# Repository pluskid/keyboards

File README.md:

# KID's Keyboard Related Code

- [flanck](flanck/): contains the PCB, plates and firmware of my first self-designed keyboard.
- [ortho-keymap](ortho-keymap/): a script that I use to manage and convert my ([Colemak-DHm](https://colemakmods.github.io/mod-dh/keyboards.html) based) keymap across multiple different ortholinear flavored keyboards (Flanck, Planck, Corne and Reviung41).
- [crkbd-kid](crkbd-kid/): my custom firmware for the [Corne](https://github.com/foostan/crkbd) split keyboard, mostly containing the code for custom OLED display.

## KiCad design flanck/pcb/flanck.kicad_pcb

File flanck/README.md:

# Flanck

Flanck is the "Fat Planck". It is a low profile 4x12 grid style keypoard using Kailh Choc Switch. The outer most columns are modified to be 1.5U wide to make it easier to hit without stretching the wrist too much. The two sides are also made 1U apart to make it more ergonomic. It also makes room for the Elite-C on the top side of the PCB, which allows us to reduce the height of the board.

## Flanck v1.1

The first built of Flanck (on Oct. 27, 2020). If you are interested in building this keyboard yourself, you will need the followings:

- The garber files of the PCB, the top plate and bottom plate can be found in the [Flanck v1.1 Release page](https://github.com/pluskid/keyboards/releases/tag/flanck-v1.1). You can order PCBs using those files from manufactures like [JLCPCB](https://jlcpcb.com/).
- The firmware is based on [QMK](https://docs.qmk.fm/), and can be found under [qmk/v1](qmk/v1/).
- The following table list the remaining components that are needed. The links are only provided for conveinence. You can collect your parts from any sources.

| Item        | Qty| Links | Remarks |
|-------------|---:|-------|---------|
| Elite-C     |  1 | [BoardSource](https://boardsource.xyz/store/5ef67ea66786dc1e65a80708), [Keeb.io](https://keeb.io/products/elite-c-low-profile-version-usb-c-pro-micro-replacement-atmega32u4) | Can also use Pro Micro and compatible clones -- then don't forget to update `BOOTLOADER` in [qmk/v1/rules.mk](qmk/v1/rules.mk) of the firmware accordinly. |
| Diode (1N4148 SMD) | 48 | [BoardSource](https://boardsource.xyz/store/5ec9fc5d64caf04f83aa646c) | |
| Choc Hotswap Socket| 48 | [BoardSource](https://boardsource.xyz/store/5eca381464caf04f83aa6482) | |
| Kailh Choc Switch  | 48 | [BoardSource](https://boardsource.xyz/store/5ef6eff1de8f0374b7347742), [AliExperss](https://www.aliexpress.com/item/4000907409650.html) | Both V1 and V2 should work, though I only tested Choc V1 |
| Choc Keycap 1U | 40 | [BoardSource MBK keycaps](https://boardsource.xyz/store/5f6ef2d68e3bf05ab838f918)| Get 2x home-scooped 1U keycaps as well |
| Choc Keycap 1.5U | 8 | [BoardSource MBK keycaps](https://boardsource.xyz/store/5f6ef2d68e3bf05ab838f918)| |
| Tact Switch |  1 | [Amazon](https://www.amazon.com/gp/product/B0819VWGX8/ref=ppx_yo_dt_b_asin_title_o09_s00?ie=UTF8&psc=1), [AliExperss](https://www.aliexpress.com/item/32914876022.html) | For the reset button |
| Rubber Feet |  6 | [Amazon](https://www.amazon.com/gp/product/B07LGK6RWN/ref=ppx_yo_dt_b_asin_title_o00_s00?ie=UTF8&psc=1), [AliExperss](https://www.aliexpress.com/item/32289191938.html) | |
| M2 4mm spacer | 7 | [Amazon](https://www.amazon.com/gp/product/B07H3VN9Y9/ref=ppx_yo_dt_b_asin_title_o02_s00?ie=UTF8&psc=1) | Longer spacers also work, though board will be higher |
| M2 screws     | 14 | [BoardSource](https://boardsource.xyz/store/5ecad681e7e0515b382b553e) | 4mm screws work for 4mm spacers. You can get some M2 washers (1mm thick) to fine tune if your spacers do not have enough room for the screws to go all the way in. |
| USB-C cable |  1 | [Amazon](https://www.amazon.com/gp/product/B07X8FNQ6K/ref=ppx_yo_dt_b_asin_title_o02_s01?ie=UTF8&psc=1) | USB-2 is enougn |
| Washers or O rings | | | Optional. See below. |

## Washers / O rings between PCB and Bottom Plate

When using Choc switches, there is ~2mm space between the PCB and the bottom plate. The PCB is held together with the top plate by the switches. If you frequently change the switches or want extra support for the PCB, you can put washers or O rings around each M2 spacer between the PCB and the bottom plate. See the illustration below:

## Wireless Flanck with nice!nano

You can use any Pro Micro compatible MCU board in place of Elite-C. In particular, I built a [nice!nano](https://docs.nicekeyboards.com/#/nice!nano/) based Flanck keyboard that support bluetooth. I use [this 3.7V 100mAh Lithium Ion Polymer Battery](https://www.amazon.com/gp/product/B0137KTPP0/ref=ppx_yo_dt_b_search_asin_title?ie=UTF8&psc=1), which is small enough to sit below the nice!nano. The [ZMK](https://zmkfirmware.dev/) based firmware can be found [here](https://github.com/pluskid/flanck-zmk-config).

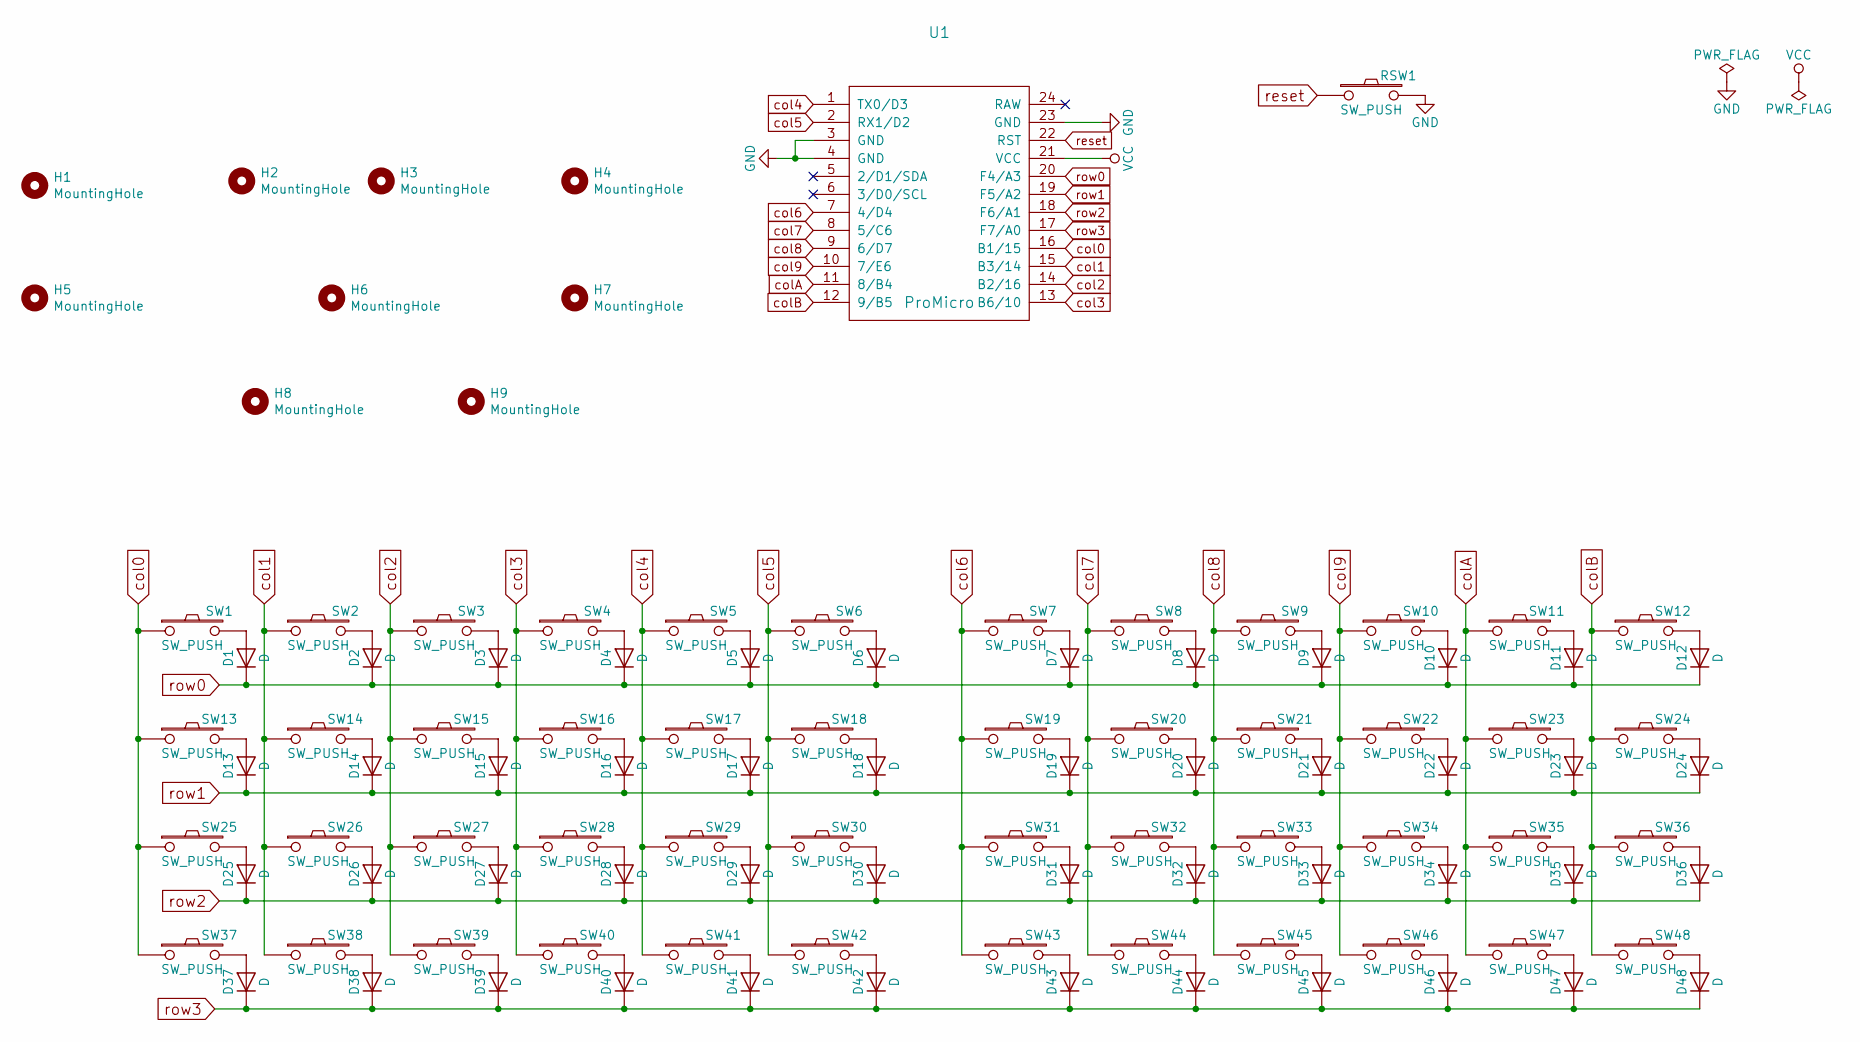
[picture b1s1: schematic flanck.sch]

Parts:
D1, D2, D3, D4, D5, D6, D7, D8, D9, D10, D11, D12, D13, D14, D15, D16, D17, D18, D19, D20, D21, D22, D23, D24, D25, D26, D27, D28, D29, D30, D31, D32, D33, D34, D35, D36, D37, D38, D39, D40, D41, D42, D43, D44, D45, D46, D47, D48: D; D3_SMD_v2
H1, H2, H3, H4, H5, H6, H7, H8, H9: MountingHole; M2_Threads_v2
RSW1: SW_PUSH; ResetSW_1side
SW1, SW12, SW13, SW24, SW25, SW36, SW42, SW43: SW_PUSH; ChocV1_V2_Hotswap_1.5u
SW2, SW3, SW4, SW5, SW6, SW7, SW8, SW9, SW10, SW11, SW14, SW15, SW16, SW17, SW18, SW19, SW20, SW21, SW22, SW23, SW26, SW27, SW28, SW29, SW30, SW31, SW32, SW33, SW34, SW35, SW37, SW38, SW39, SW40, SW41, SW44, SW45, SW46, SW47, SW48: SW_PUSH; ChocV1_V2_Hotswap
U1: ProMicro; ProMicro_v3

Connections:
GND: RSW1.2, U1.3 (GND), U1.4 (GND), U1.23 (GND)
unnamed: D1.2 (A), SW1.2
unnamed: D2.2 (A), SW2.2
unnamed: D3.2 (A), SW3.2
unnamed: D4.2 (A), SW4.2
unnamed: D5.2 (A), SW5.2
unnamed: D6.2 (A), SW6.2
unnamed: D7.2 (A), SW7.2
unnamed: D8.2 (A), SW8.2
unnamed: D9.2 (A), SW9.2
unnamed: D10.2 (A), SW10.2
unnamed: D11.2 (A), SW11.2
unnamed: D12.2 (A), SW12.2
unnamed: D13.2 (A), SW13.2
unnamed: D14.2 (A), SW14.2
unnamed: D15.2 (A), SW15.2
unnamed: D16.2 (A), SW16.2
unnamed: D17.2 (A), SW17.2
unnamed: D18.2 (A), SW18.2
unnamed: D19.2 (A), SW19.2
unnamed: D20.2 (A), SW20.2
unnamed: D21.2 (A), SW21.2
unnamed: D22.2 (A), SW22.2
unnamed: D23.2 (A), SW23.2
unnamed: D24.2 (A), SW24.2
unnamed: D25.2 (A), SW25.2
unnamed: D26.2 (A), SW26.2
unnamed: D27.2 (A), SW27.2
unnamed: D28.2 (A), SW28.2
unnamed: D29.2 (A), SW29.2
unnamed: D30.2 (A), SW30.2
unnamed: D31.2 (A), SW31.2
unnamed: D32.2 (A), SW32.2
unnamed: D33.2 (A), SW33.2
unnamed: D34.2 (A), SW34.2
unnamed: D35.2 (A), SW35.2
unnamed: D36.2 (A), SW36.2
unnamed: D37.2 (A), SW37.2
unnamed: D38.2 (A), SW38.2
unnamed: D39.2 (A), SW39.2
unnamed: D40.2 (A), SW40.2
unnamed: D41.2 (A), SW41.2
unnamed: D42.2 (A), SW42.2
unnamed: D43.2 (A), SW43.2
unnamed: D44.2 (A), SW44.2
unnamed: D45.2 (A), SW45.2
unnamed: D46.2 (A), SW46.2
unnamed: D47.2 (A), SW47.2
unnamed: D48.2 (A), SW48.2
VCC: U1.21 (VCC)
col0: SW1.1, SW13.1, SW25.1, SW37.1, U1.16 (B1/15)
col1: SW2.1, SW14.1, SW26.1, SW38.1, U1.15 (B3/14)
col2: SW3.1, SW15.1, SW27.1, SW39.1, U1.14 (B2/16)
col3: SW4.1, SW16.1, SW28.1, SW40.1, U1.13 (B6/10)
col4: SW5.1, SW17.1, SW29.1, SW41.1, U1.1 (TX0/D3)
col5: SW6.1, SW18.1, SW30.1, SW42.1, U1.2 (RX1/D2)
col6: SW7.1, SW19.1, SW31.1, SW43.1, U1.7 (4/D4)
col7: SW8.1, SW20.1, SW32.1, SW44.1, U1.8 (5/C6)
col8: SW9.1, SW21.1, SW33.1, SW45.1, U1.9 (6/D7)
col9: SW10.1, SW22.1, SW34.1, SW46.1, U1.10 (7/E6)
colA: SW11.1, SW23.1, SW35.1, SW47.1, U1.11 (8/B4)
colB: SW12.1, SW24.1, SW36.1, SW48.1, U1.12 (9/B5)
reset: RSW1.1, U1.22 (RST)
row0: D1.1 (K), D2.1 (K), D3.1 (K), D4.1 (K), D5.1 (K), D6.1 (K), D7.1 (K), D8.1 (K), D9.1 (K), D10.1 (K), D11.1 (K), D12.1 (K), U1.20 (F4/A3)
row1: D13.1 (K), D14.1 (K), D15.1 (K), D16.1 (K), D17.1 (K), D18.1 (K), D19.1 (K), D20.1 (K), D21.1 (K), D22.1 (K), D23.1 (K), D24.1 (K), U1.19 (F5/A2)
row2: D25.1 (K), D26.1 (K), D27.1 (K), D28.1 (K), D29.1 (K), D30.1 (K), D31.1 (K), D32.1 (K), D33.1 (K), D34.1 (K), D35.1 (K), D36.1 (K), U1.18 (F6/A1)
row3: D37.1 (K), D38.1 (K), D39.1 (K), D40.1 (K), D41.1 (K), D42.1 (K), D43.1 (K), D44.1 (K), D45.1 (K), D46.1 (K), D47.1 (K), D48.1 (K), U1.17 (F7/A0)

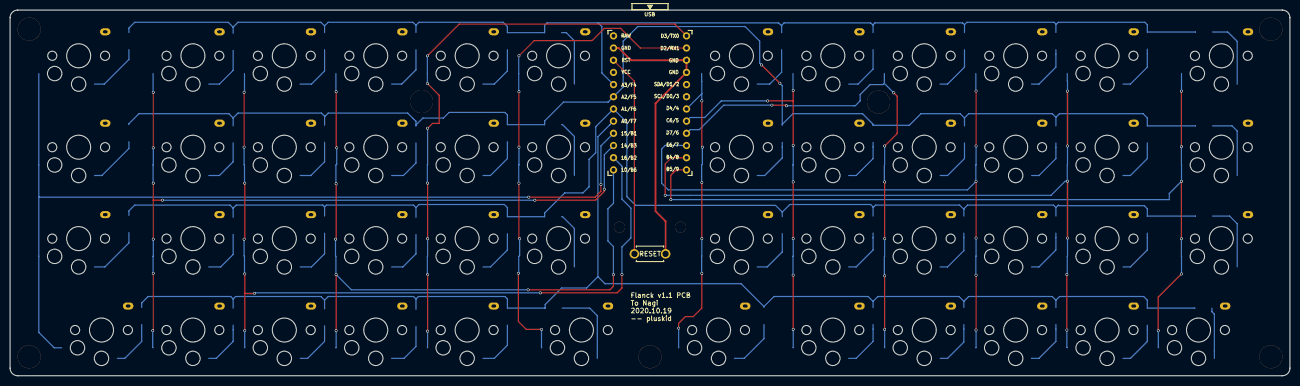
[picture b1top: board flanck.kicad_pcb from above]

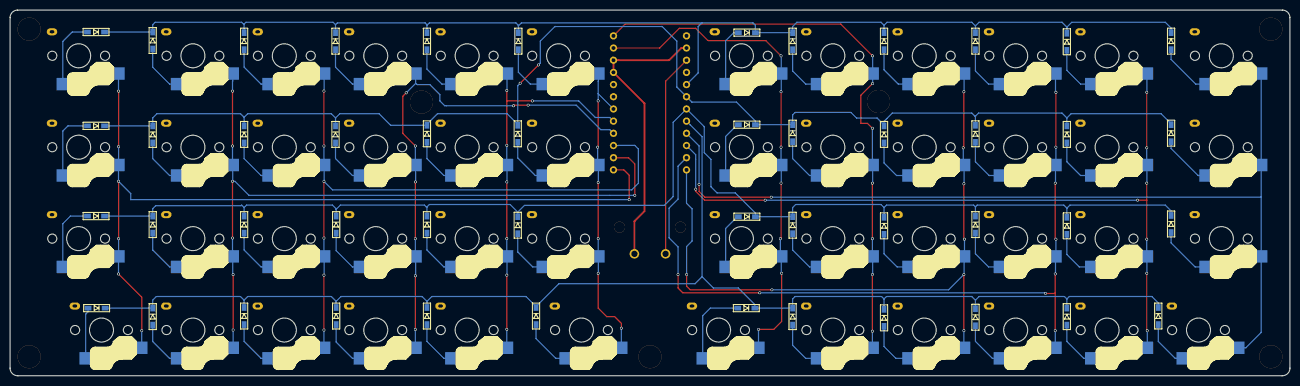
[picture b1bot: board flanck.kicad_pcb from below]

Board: 2 copper layers, 266.7 x 76.2 mm, 107 parts (49 on the bottom side), 66 nets.

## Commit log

2020-10-12 crkbd colemak layout
2020-10-15 one-side of LED working
2020-10-18 oled functionality
2020-10-18 add foostan kbd submodule
2020-10-19 flanck pcb
2020-10-19 copy pcb to plate file
2020-10-19 update submodule
2020-10-19 force adding kbd submodule twice
2020-10-19 copy top plate as bottom plate
2020-10-19 add submodule for bottom plate
2020-10-19 bottom plate
2020-10-19 fix pcb mounting hole sizes
2020-10-20 updated drill hole size per JLCPCB feedback
2020-10-21 flanck firmware and default keymap
2020-10-25 basic qmk layout converter
2020-10-25 add readme
2020-10-25 cleanup rgb-led code and add README.
2020-10-25 add MIT license
2020-10-25 update corne keymap
2020-10-25 clean up unused code
2020-10-28 update readme of flanck firmware
2020-10-28 update flanck keymap
2020-10-28 update readme file
2020-10-28 rename readme file
2020-10-28 fix relative URLs
2020-10-28 fix URL
2020-11-02 swap left and right shift
2020-11-03 tweak mod-tap behavior
2020-11-04 information for o-ring and bluetooth Flanck
2020-11-04 Add Flanck wireless picture
2020-11-04 Add BOM for hot swap socket
2020-11-04 replace the arrow keys with mirrored modifiers
2020-11-17 change the location of rctl mod tap
2020-11-29 modify tapping term
2021-03-13 update keymap
2021-03-22 add qwer based keymap
2021-09-19 update flanck to be qwer
2021-10-31 add rshift-symbol keymap
2021-10-31 update qmk to latest version
2022-07-01 refine flanck keymap and make it compatible with latest qmk
